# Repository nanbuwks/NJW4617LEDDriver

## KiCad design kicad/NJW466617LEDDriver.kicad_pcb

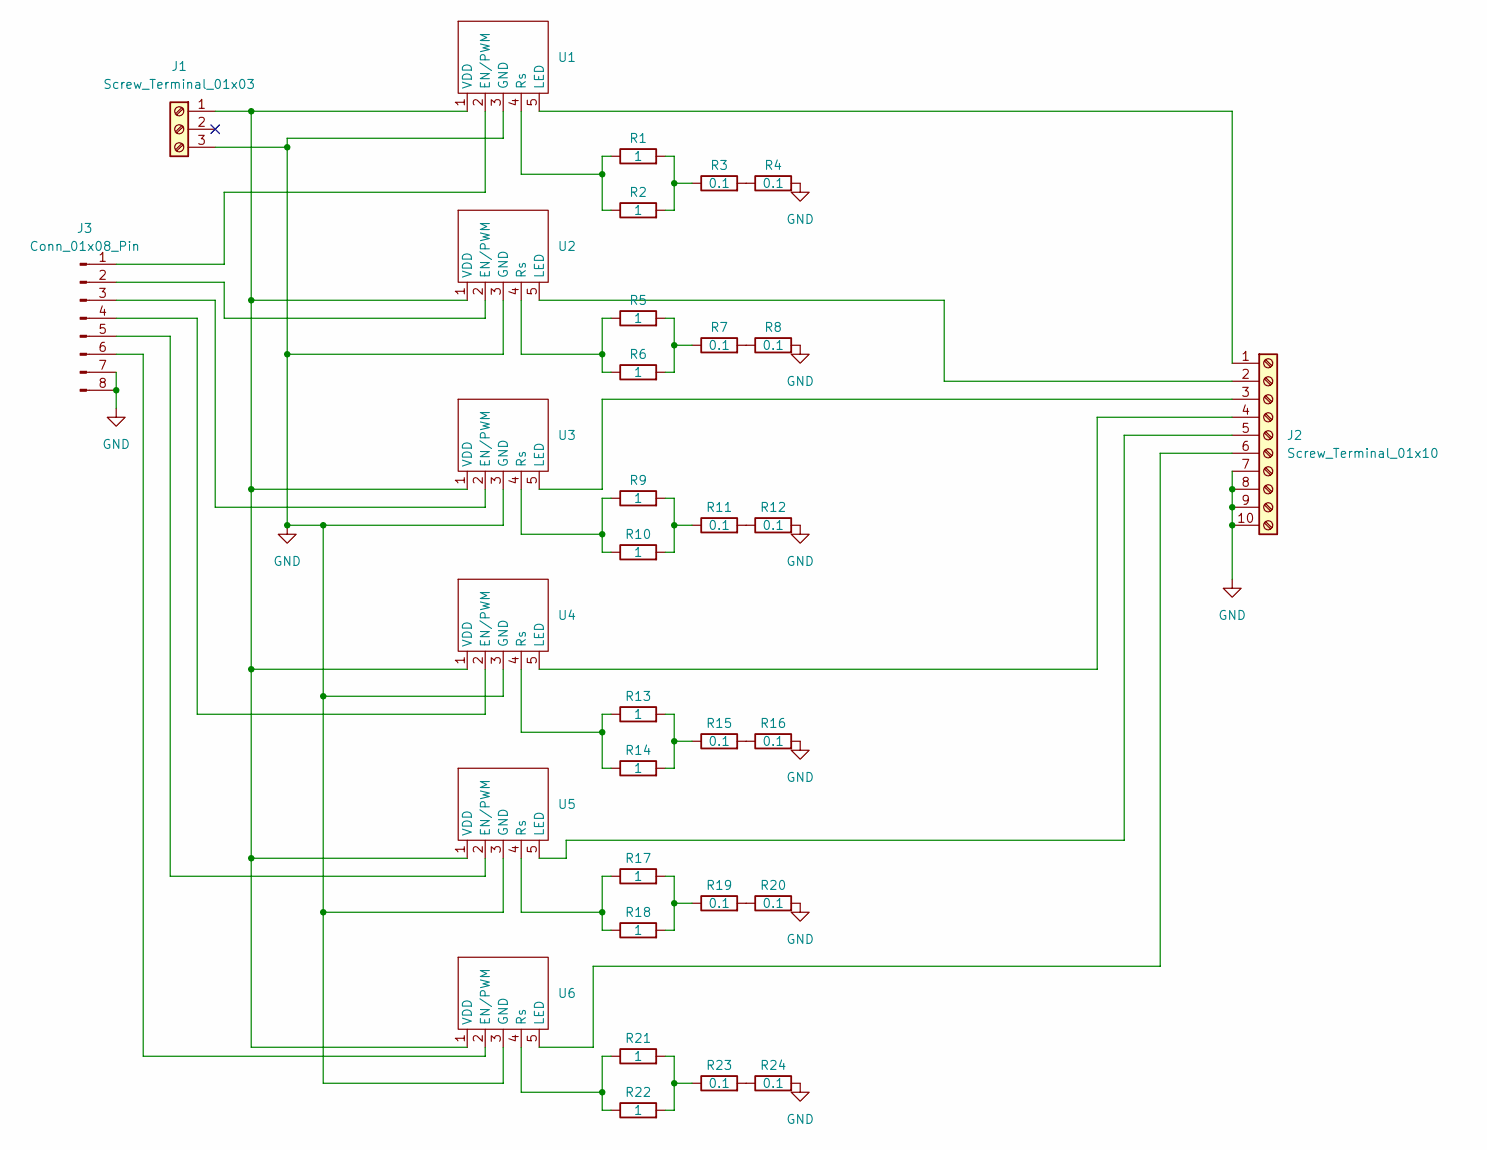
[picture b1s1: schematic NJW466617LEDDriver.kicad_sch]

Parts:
J1: Screw_Terminal_01x03; TerminalBlock_MetzConnect_Type067_RT01903HDWC_1x03_P10.00mm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
J2: Screw_Terminal_01x10; TerminalBlock_RND_205-00031_1x10_P10.00mm_Horizontal
J3: Conn_01x08_Pin; PinHeader_1x08_P2.54mm_Vertical
R1, R2, R5, R6, R9, R10, R13, R14, R17, R18, R21, R22: 1; R_Axial_DIN0207_L6.3mm_D2.5mm_P7.62mm_Horizontal
R3, R4, R7, R8, R11, R12, R15, R16, R19, R20, R23, R24: 0.1; R_Axial_DIN0207_L6.3mm_D2.5mm_P7.62mm_Horizontal
U1, U2, U3, U4, U5, U6: TerminalBlock_Phoenix_MPT-0,5-5-2.54_1x05_P2.54mm_Horizontal

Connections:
GND: J1.3, J2.7, J2.8, J2.9, J2.10, J3.7, J3.8, R4.2, R8.2, R12.2, R16.2, R20.2, R24.2, U1.3 (GND), U2.3 (GND), U3.3 (GND), U4.3 (GND), U5.3 (GND), U6.3 (GND)
unnamed: J1.1, U1.1 (VDD), U2.1 (VDD), U3.1 (VDD), U4.1 (VDD), U5.1 (VDD), U6.1 (VDD)
unnamed: J2.1, U1.5 (LED)
unnamed: J2.2, U2.5 (LED)
unnamed: J2.3, U3.5 (LED)
unnamed: J2.4, U4.5 (LED)
unnamed: J2.5, U5.5 (LED)
unnamed: J2.6, U6.5 (LED)
unnamed: J3.1, U1.2 (EN/PWM)
unnamed: J3.2, U2.2 (EN/PWM)
unnamed: J3.3, U3.2 (EN/PWM)
unnamed: J3.4, U4.2 (EN/PWM)
unnamed: J3.5, U5.2 (EN/PWM)
unnamed: J3.6, U6.2 (EN/PWM)
unnamed: R1.2, R2.2, R3.1
unnamed: R3.2, R4.1
unnamed: R5.2, R6.2, R7.1
unnamed: R7.2, R8.1
unnamed: R9.2, R10.2, R11.1
unnamed: R11.2, R12.1
unnamed: R13.2, R14.2, R15.1
unnamed: R15.2, R16.1
unnamed: R17.2, R18.2, R19.1
unnamed: R19.2, R20.1
unnamed: R21.2, R22.2, R23.1
unnamed: R23.2, R24.1
unnamed: R1.1, R2.1, U1.4 (Rs)
unnamed: R5.1, R6.1, U2.4 (Rs)
unnamed: R9.1, R10.1, U3.4 (Rs)
unnamed: R13.1, R14.1, U4.4 (Rs)
unnamed: R17.1, R18.1, U5.4 (Rs)
unnamed: R21.1, R22.1, U6.4 (Rs)

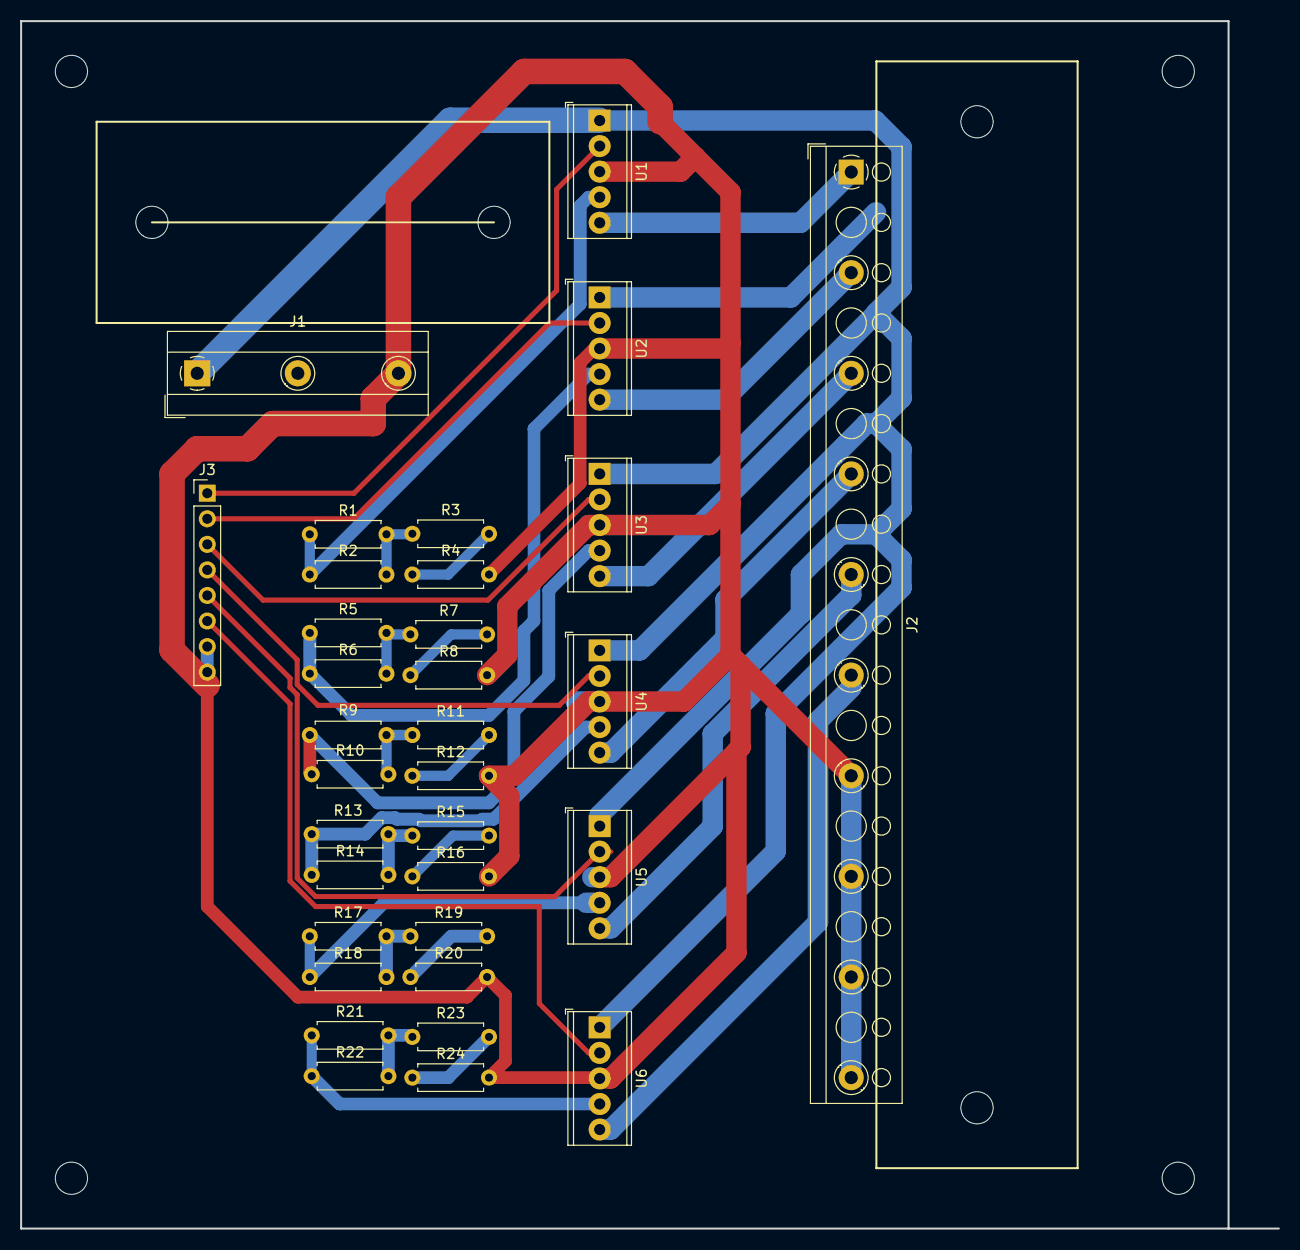
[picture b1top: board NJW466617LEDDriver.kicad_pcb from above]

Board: 2 copper layers, 125.0 x 120.0 mm, 33 parts (0 on the bottom side), 32 nets.

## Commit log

2024-10-20 20241018version
